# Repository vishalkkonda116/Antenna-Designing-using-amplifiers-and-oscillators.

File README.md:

# Antenna-Designing-using-amplifiers-and-oscillators.

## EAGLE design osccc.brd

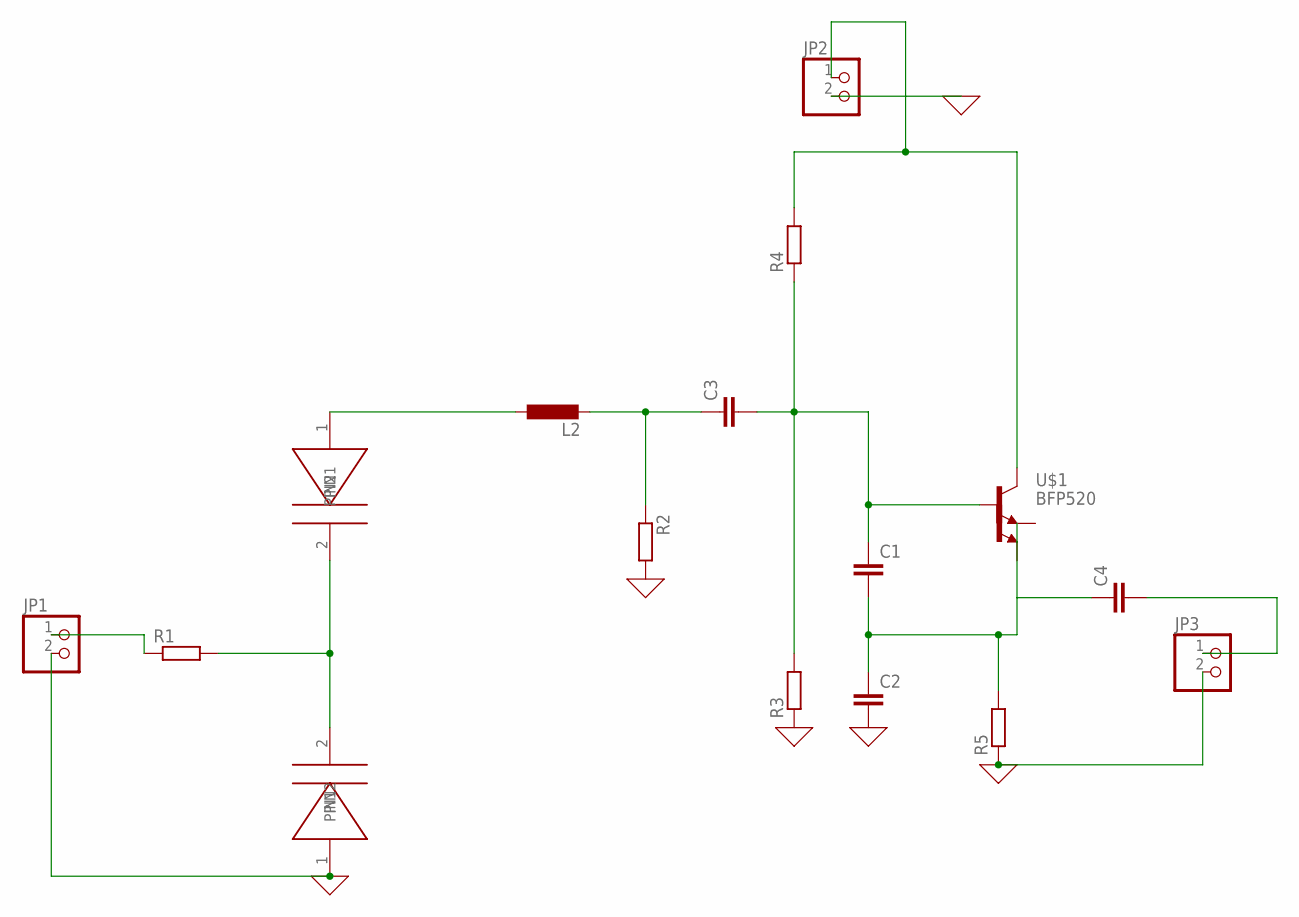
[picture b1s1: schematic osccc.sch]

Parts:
C1, C2, C3, C4: C-EUC0603; C0603
JP1, JP2, JP3: PINHD-1X2; 1X02
L2: L-EUL0603; L0603
R1, R2, R3, R4, R5: R-EU_R0603; R0603
U$1: BFP520; SOT343
U$2, U$3: BBY5702

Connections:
0: C2.2, JP1.2, JP2.2, JP3.2, R2.2, R3.1, R5.1, U$2.1 (PIN1)
unnamed: R1.2, U$2.2 (PIN2), U$3.2 (PIN2)
unnamed: L2.1, U$3.1 (PIN1)
unnamed: C3.1, L2.2, R2.1
unnamed: C1.1, C3.2, R3.2, R4.1, U$1.1 (B)
unnamed: C1.2, C2.1, C4.1, R5.2, U$1.2 (E1), U$1.4 (E2)
unnamed: JP2.1, R4.2, U$1.3 (C)
unnamed: JP1.1, R1.1
unnamed: C4.2, JP3.1

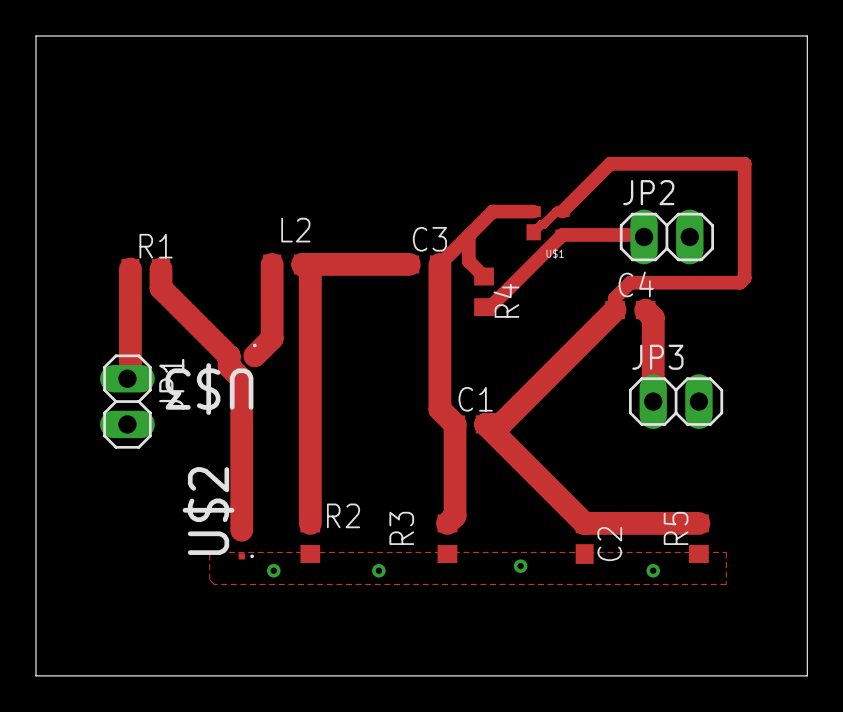
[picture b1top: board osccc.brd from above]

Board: 2 copper layers, 42.9 x 35.5 mm, 16 parts (0 on the bottom side), 9 nets.

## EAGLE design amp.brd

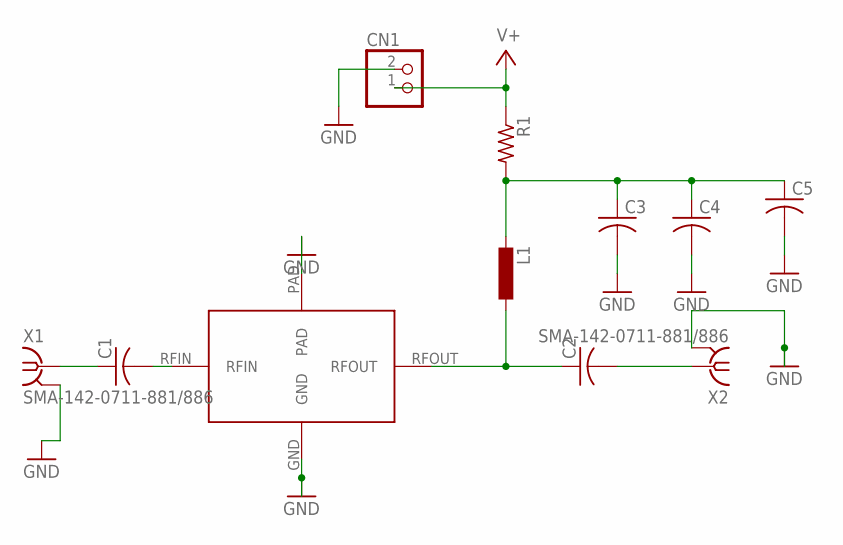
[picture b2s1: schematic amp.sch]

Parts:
C1, C2, C3, C4, C5: C-USC0603; C0603
CN1: JST_2PIN-THM; JST-PH-2-THM
L1: L-EUL0603; L0603
R1: R-US_R0603; R0603
U$1: MMG3001; SOT-89
X1, X2: SMA-142-0711-881/886; J502-ND-142-0711-881/886

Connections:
GND: C3.2, C4.2, C5.2, CN1.2 (1), U$1.GND, U$1.PAD, X1.G@1 (2), X1.G@2 (2), X1.G@3 (2), X1.G@4 (2), X2.G@1 (2), X2.G@2 (2), X2.G@3 (2), X2.G@4 (2)
unnamed: C1.1, X1.1
unnamed: C3.1, C4.1, C5.1, L1.2, R1.2
unnamed: C2.1, L1.1, U$1.RFOUT
unnamed: C1.2, U$1.RFIN
unnamed: C2.2, X2.1
V+: CN1.1 (2), R1.1

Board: 2 copper layers, 11 parts (0 on the bottom side), 7 nets, no tracks yet.
